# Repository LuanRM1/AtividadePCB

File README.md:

# AtividadePCB (esse read.me foi criado com ajuda do chat GPT-4.0)

Este repositório contém os arquivos fundamentais para a compreensão e reprodução de um design de circuito eletrônico. Ele inclui os arquivos de design da Placa de Circuito Impresso (PCB) e os desenhos esquemáticos do projeto.

## Sobre os Arquivos no Repositório

O projeto é composto por dois tipos principais de arquivos que são cruciais para o entendimento e a construção física do circuito eletrônico:

### Arquivos Esquemáticos (`_sch`)

- **Propósito**: Os arquivos esquemáticos representam a conexão teórica entre os componentes do circuito. Eles são usados para ilustrar a função do circuito e como os componentes são interligados.

### Arquivos de PCB (`_pcb`)

- **Propósito**: Os arquivos de PCB contêm o layout físico da placa, incluindo a posição dos componentes, trilhas de cobre, vias e outras especificações físicas do design. Eles são utilizados para fabricar a placa de circuito impresso.
- **Como Usar**: Assim como os arquivos esquemáticos, os arquivos de PCB necessitam de um software de design de PCB para serem abertos e editados. Estes arquivos são críticos para a produção da placa, fornecendo detalhes exatos de dimensionamento, camadas e posicionamento dos componentes.

## Pré-requisitos

Para trabalhar com esses arquivos, você precisará instalar um software de design eletrônico que suporte os formatos `.sch` para esquemáticos e `.pcb` para design de placa. 

- [KiCad](https://www.kicad.org/download/)

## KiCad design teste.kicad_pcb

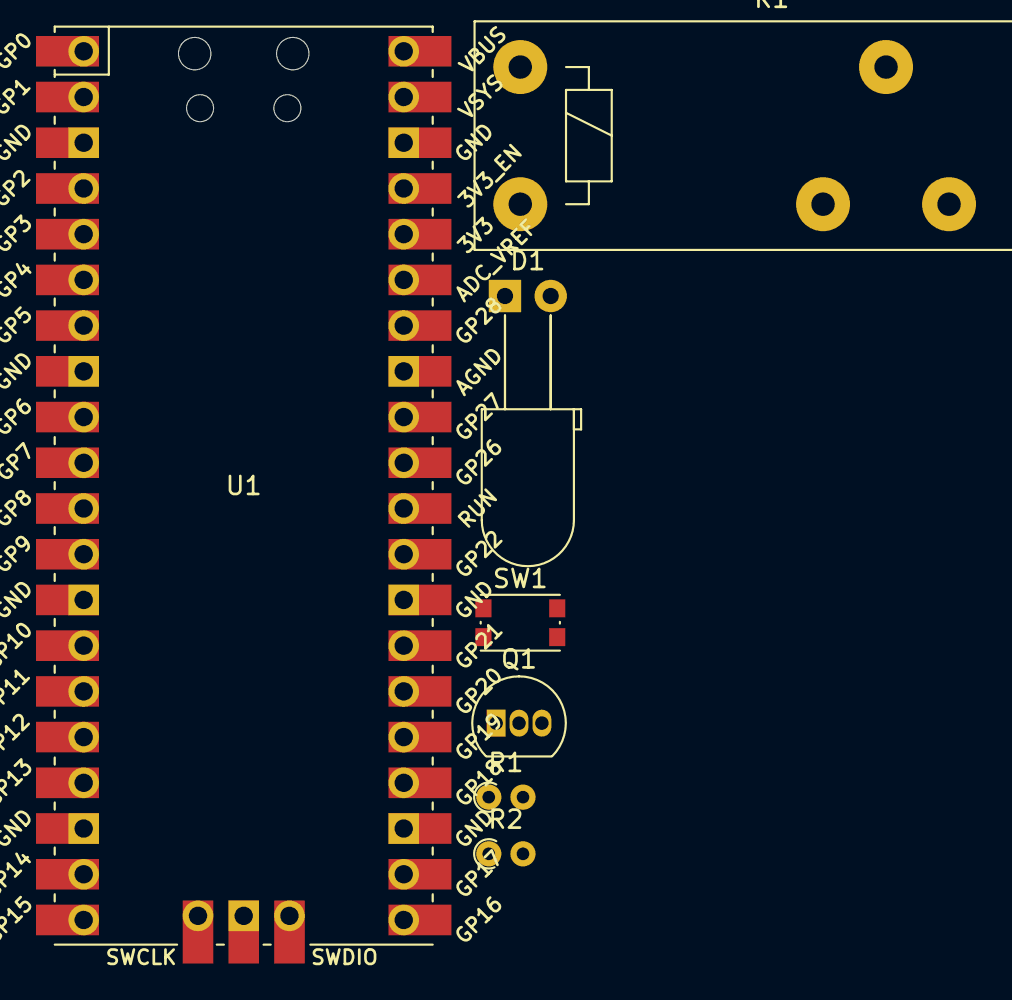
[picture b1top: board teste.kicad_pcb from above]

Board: 2 copper layers, 7 parts (0 on the bottom side), 7 nets, no tracks yet.

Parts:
D1: LED; LED_D5.0mm_Horizontal_O6.35mm_Z15.0mm
K1: Relay_SPST-NO; Relay_SPDT_Schrack-RP-II-1-FormC_RM3.5mm
Q1: BC548; TO-92_Inline
R1, R2: R; R_Axial_DIN0204_L3.6mm_D1.6mm_P1.90mm_Vertical
SW1: SW_Push; SW_Push_1P1T_NO_CK_KMR2
U1: Pico; RPi_Pico_SMD_TH

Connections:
GND: D1.1 (K), Q1.3 (E), SW1.2
GPIO20: R2.1, U1.26 (GPIO20)
GPIO21: SW1.1, U1.27 (GPIO21)
LED: K1.14, R1.2
unnamed: D1.2 (A), R1.1
unnamed: Q1.2 (B), R2.2
TRANSISTOR: K1.A1, Q1.1 (C)
